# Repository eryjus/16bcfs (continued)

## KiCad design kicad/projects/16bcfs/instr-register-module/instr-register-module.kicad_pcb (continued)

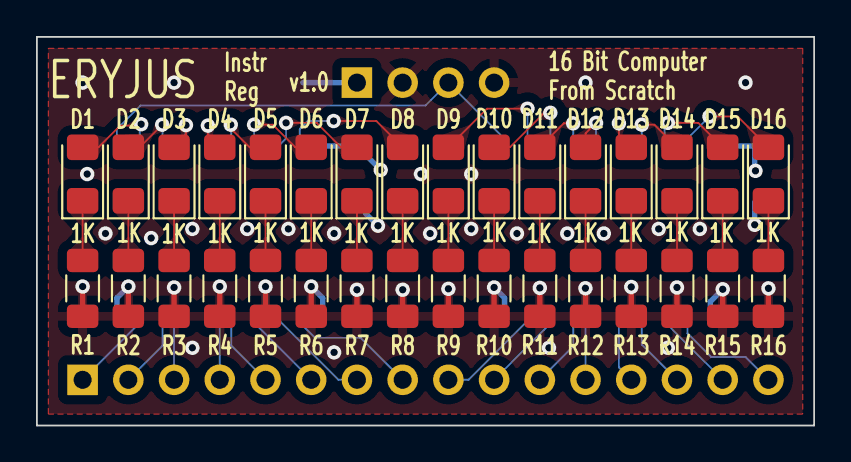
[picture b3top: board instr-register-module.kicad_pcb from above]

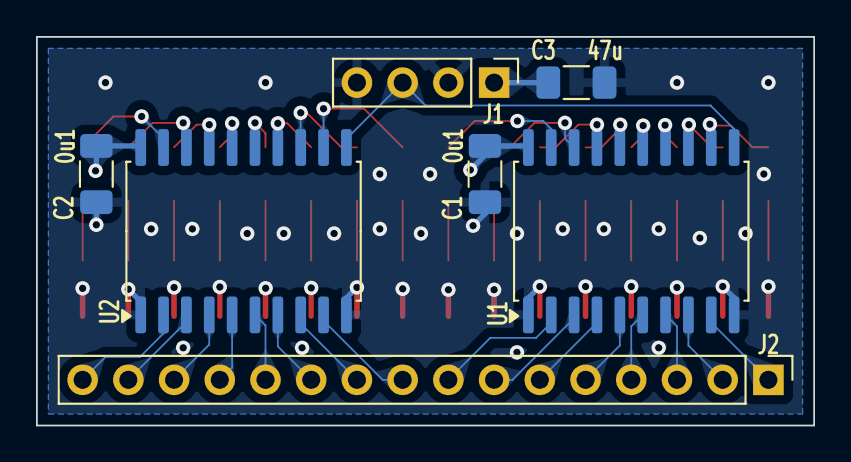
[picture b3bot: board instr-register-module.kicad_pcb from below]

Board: 4 copper layers, 43.2 x 21.6 mm, 39 parts (7 on the bottom side), 51 nets.

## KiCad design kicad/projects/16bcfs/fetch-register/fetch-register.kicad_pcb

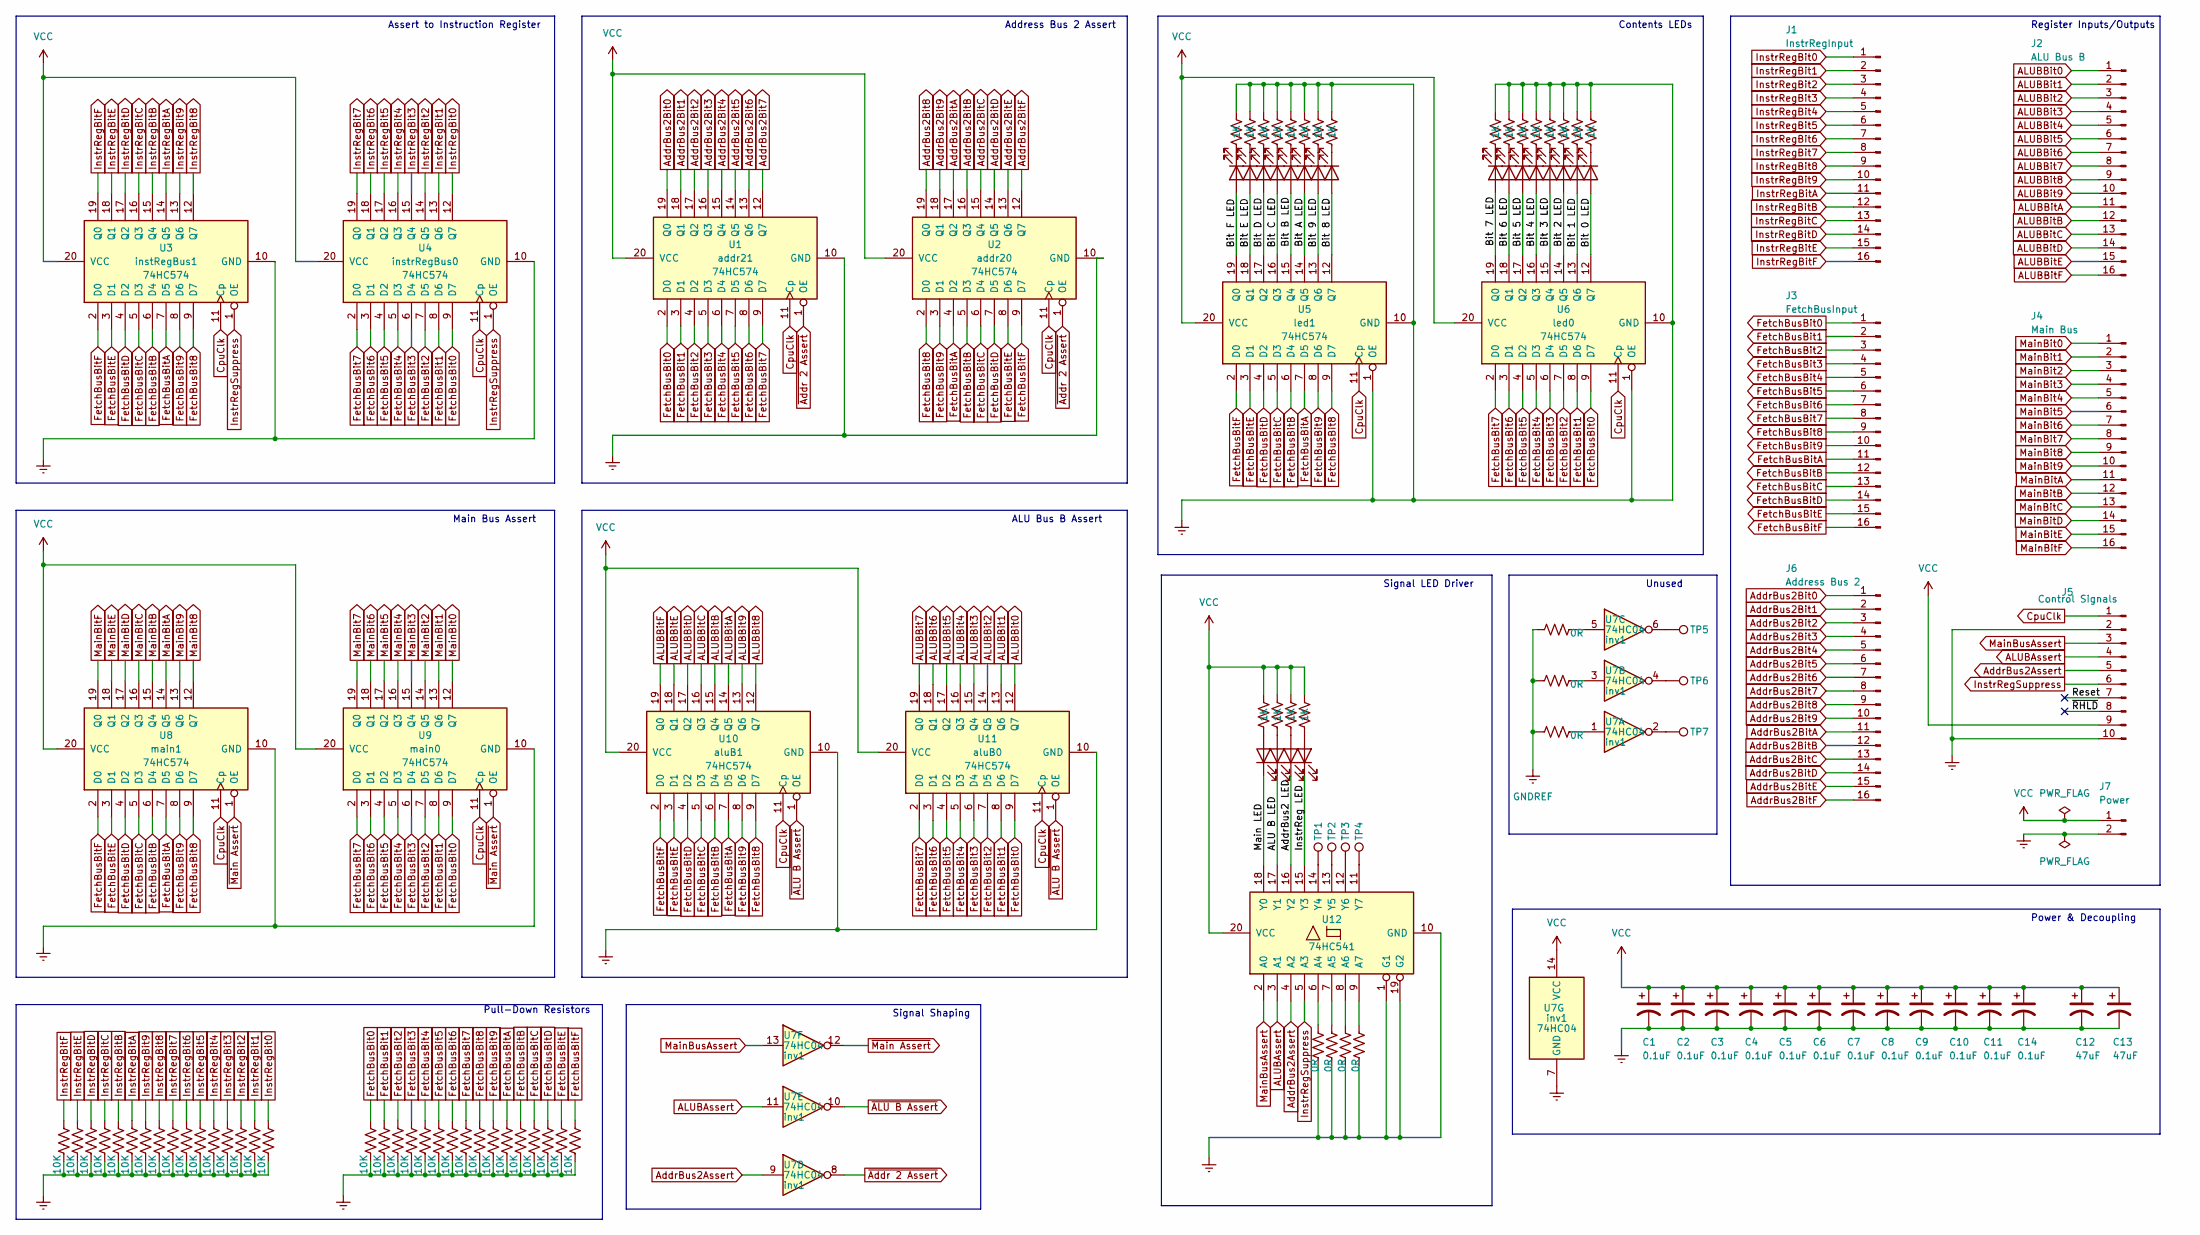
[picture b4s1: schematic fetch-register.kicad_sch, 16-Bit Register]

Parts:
C1, C2, C3, C4, C5, C6, C7, C8, C9, C10, C11, C14: 0.1uF; C_1206_3216Metric_Pad1.33x1.80mm_HandSolder
C12, C13: 47uF; C_1206_3216Metric_Pad1.33x1.80mm_HandSolder
D1, D2, D3, D4, D5, D6, D7, D8, D9, D10, D11, D12, D13, D14, D15, D16: Green; LED_1206_3216Metric_Pad1.42x1.75mm_HandSolder
D17, D18, D19, D20: Red; LED_1206_3216Metric_Pad1.42x1.75mm_HandSolder
J1: InstrRegInput; PinHeader_1x16_P2.54mm_Vertical
J2: ALU Bus B; PinHeader_1x16_P2.54mm_Vertical
J3: FetchBusInput; PinHeader_1x16_P2.54mm_Vertical
J4: Main Bus; PinHeader_1x16_P2.54mm_Vertical
J5: Control Signals; PinHeader_1x10_P2.54mm_Vertical
J6: Address Bus 2; PinHeader_1x16_P2.54mm_Vertical
J7: Power; PinHeader_1x02_P2.54mm_Vertical
R1, R2, R3, R4, R5, R6, R7, R8, R9, R10, R11, R12, R13, R14, R15, R16, R17, R18, R19, R20: 1K; R_1206_3216Metric_Pad1.30x1.75mm_HandSolder
R21, R22, R23, R24, R25, R26, R27, R28, R29, R30, R31, R32, R33, R34, R35, R36, R37, R38, R39, R40, R41, R42, R43, R44, R45, R46, R47, R48, R49, R50, R51, R52: 10K; R_1206_3216Metric_Pad1.30x1.75mm_HandSolder
R53, R54, R55, R56, R57, R58, R59: 0R; R_1206_3216Metric_Pad1.30x1.75mm_HandSolder
TP1, TP2, TP3, TP4, TP5, TP6, TP7: TestPoint; TestPoint_SMD_D0.8mm
U1, U2, U3, U4, U5, U6, U8, U9, U10, U11: 74HC574; SOIC-20W_7.5x12.8mm_P1.27mm
U7: 74HC04; SOIC-14_3.9x8.7mm_P1.27mm
U12: 74HC541; SOIC-20W_7.5x12.8mm_P1.27mm

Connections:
/ALU B LED: D18.1 (K), U12.17 (Y1)
/AddrBus2 LED: D19.1 (K), U12.16 (Y2)
/Bit 0 LED: D16.2 (A), U6.12 (Q7)
/Bit 1 LED: D15.2 (A), U6.13 (Q6)
/Bit 2 LED: D14.2 (A), U6.14 (Q5)
/Bit 3 LED: D13.2 (A), U6.15 (Q4)
/Bit 4 LED: D12.2 (A), U6.16 (Q3)
/Bit 5 LED: D11.2 (A), U6.17 (Q2)
/Bit 6 LED: D10.2 (A), U6.18 (Q1)
/Bit 7 LED: D9.2 (A), U6.19 (Q0)
/Bit 8 LED: D8.2 (A), U5.12 (Q7)
/Bit 9 LED: D7.2 (A), U5.13 (Q6)
/Bit A LED: D6.2 (A), U5.14 (Q5)
/Bit B LED: D5.2 (A), U5.15 (Q4)
/Bit C LED: D4.2 (A), U5.16 (Q3)
/Bit D LED: D3.2 (A), U5.17 (Q2)
/Bit E LED: D2.2 (A), U5.18 (Q1)
/Bit F LED: D1.2 (A), U5.19 (Q0)
/InstrReg LED: D20.1 (K), U12.15 (Y3)
/Main LED: D17.1 (K), U12.18 (Y0)
/Reset: J5.7
/~RHLD: J5.8
ALUBAssert: J5.4, U7.11, U12.3 (A1)
ALUBBit0: J2.1, U11.12 (Q7)
ALUBBit1: J2.2, U11.13 (Q6)
ALUBBit2: J2.3, U11.14 (Q5)
ALUBBit3: J2.4, U11.15 (Q4)
ALUBBit4: J2.5, U11.16 (Q3)
ALUBBit5: J2.6, U11.17 (Q2)
ALUBBit6: J2.7, U11.18 (Q1)
ALUBBit7: J2.8, U11.19 (Q0)
ALUBBit8: J2.9, U10.12 (Q7)
ALUBBit9: J2.10, U10.13 (Q6)
ALUBBitA: J2.11, U10.14 (Q5)
ALUBBitB: J2.12, U10.15 (Q4)
ALUBBitC: J2.13, U10.16 (Q3)
ALUBBitD: J2.14, U10.17 (Q2)
ALUBBitE: J2.15, U10.18 (Q1)
ALUBBitF: J2.16, U10.19 (Q0)
AddrBus2Assert: J5.5, U7.9, U12.4 (A2)
AddrBus2Bit0: J6.1, U1.19 (Q0)
AddrBus2Bit1: J6.2, U1.18 (Q1)
AddrBus2Bit2: J6.3, U1.17 (Q2)
AddrBus2Bit3: J6.4, U1.16 (Q3)
AddrBus2Bit4: J6.5, U1.15 (Q4)
AddrBus2Bit5: J6.6, U1.14 (Q5)
AddrBus2Bit6: J6.7, U1.13 (Q6)
AddrBus2Bit7: J6.8, U1.12 (Q7)
AddrBus2Bit8: J6.9, U2.19 (Q0)
AddrBus2Bit9: J6.10, U2.18 (Q1)
AddrBus2BitA: J6.11, U2.17 (Q2)
AddrBus2BitB: J6.12, U2.16 (Q3)
AddrBus2BitC: J6.13, U2.15 (Q4)
AddrBus2BitD: J6.14, U2.14 (Q5)
AddrBus2BitE: J6.15, U2.13 (Q6)
AddrBus2BitF: J6.16, U2.12 (Q7)
CpuClk: J5.1, U1.11 (Cp), U2.11 (Cp), U3.11 (Cp), U4.11 (Cp), U5.11 (Cp), U6.11 (Cp), U8.11 (Cp), U9.11 (Cp), U10.11 (Cp), U11.11 (Cp)
FetchBusBit0: J3.1, R37.1, U1.2 (D0), U4.9 (D7), U6.9 (D7), U9.9 (D7), U11.9 (D7)
FetchBusBit1: J3.2, R38.1, U1.3 (D1), U4.8 (D6), U6.8 (D6), U9.8 (D6), U11.8 (D6)
FetchBusBit2: J3.3, R39.1, U1.4 (D2), U4.7 (D5), U6.7 (D5), U9.7 (D5), U11.7 (D5)
FetchBusBit3: J3.4, R40.1, U1.5 (D3), U4.6 (D4), U6.6 (D4), U9.6 (D4), U11.6 (D4)
FetchBusBit4: J3.5, R41.1, U1.6 (D4), U4.5 (D3), U6.5 (D3), U9.5 (D3), U11.5 (D3)
FetchBusBit5: J3.6, R42.1, U1.7 (D5), U4.4 (D2), U6.4 (D2), U9.4 (D2), U11.4 (D2)
FetchBusBit6: J3.7, R43.1, U1.8 (D6), U4.3 (D1), U6.3 (D1), U9.3 (D1), U11.3 (D1)
FetchBusBit7: J3.8, R44.1, U1.9 (D7), U4.2 (D0), U6.2 (D0), U9.2 (D0), U11.2 (D0)
FetchBusBit8: J3.9, R45.1, U2.2 (D0), U3.9 (D7), U5.9 (D7), U8.9 (D7), U10.9 (D7)
FetchBusBit9: J3.10, R46.1, U2.3 (D1), U3.8 (D6), U5.8 (D6), U8.8 (D6), U10.8 (D6)
FetchBusBitA: J3.11, R47.1, U2.4 (D2), U3.7 (D5), U5.7 (D5), U8.7 (D5), U10.7 (D5)
FetchBusBitB: J3.12, R48.1, U2.5 (D3), U3.6 (D4), U5.6 (D4), U8.6 (D4), U10.6 (D4)
FetchBusBitC: J3.13, R49.1, U2.6 (D4), U3.5 (D3), U5.5 (D3), U8.5 (D3), U10.5 (D3)
FetchBusBitD: J3.14, R50.1, U2.7 (D5), U3.4 (D2), U5.4 (D2), U8.4 (D2), U10.4 (D2)
FetchBusBitE: J3.15, R51.1, U2.8 (D6), U3.3 (D1), U5.3 (D1), U8.3 (D1), U10.3 (D1)
FetchBusBitF: J3.16, R52.1, U2.9 (D7), U3.2 (D0), U5.2 (D0), U8.2 (D0), U10.2 (D0)
GNDREF: C1.2, C2.2, C3.2, C4.2, C5.2, C6.2, C7.2, C8.2, C9.2, C10.2, C11.2, C12.2, C13.2, C14.2, J5.2, J5.10, J7.2, R1.1, R2.1, R3.1, R4.1, R5.1, R6.1, R7.1, R8.1, R9.1, R10.1, R11.1, R12.1, R13.1, R14.1, R15.1, R16.1, R21.2, R22.2, R23.2, R24.2, R25.2, R26.2, R27.2, R28.2, R29.2, R30.2, R31.2, R32.2, R33.2, R34.2, R35.2, R36.2, R37.2, R38.2, R39.2, R40.2, R41.2, R42.2, R43.2, R44.2, R45.2, R46.2, R47.2, R48.2, R49.2, R50.2, R51.2, R52.2, R53.2, R54.2, R55.2, R56.2, R57.1, R58.1, R59.1, U1.10 (GND), U2.10 (GND), U3.10 (GND), U4.10 (GND), U5.1 (OE), U5.10 (GND), U6.1 (OE), U6.10 (GND), U7.7 (GND), U8.10 (GND), U9.10 (GND), U10.10 (GND), U11.10 (GND), U12.1 (G1), U12.10 (GND), U12.19 (G2)
InstrRegBit0: J1.1, R36.1, U4.12 (Q7)
InstrRegBit1: J1.2, R35.1, U4.13 (Q6)
InstrRegBit2: J1.3, R34.1, U4.14 (Q5)
InstrRegBit3: J1.4, R33.1, U4.15 (Q4)
InstrRegBit4: J1.5, R32.1, U4.16 (Q3)
InstrRegBit5: J1.6, R31.1, U4.17 (Q2)
InstrRegBit6: J1.7, R30.1, U4.18 (Q1)
InstrRegBit7: J1.8, R29.1, U4.19 (Q0)
InstrRegBit8: J1.9, R28.1, U3.12 (Q7)
InstrRegBit9: J1.10, R27.1, U3.13 (Q6)
InstrRegBitA: J1.11, R26.1, U3.14 (Q5)
InstrRegBitB: J1.12, R25.1, U3.15 (Q4)
InstrRegBitC: J1.13, R24.1, U3.16 (Q3)
InstrRegBitD: J1.14, R23.1, U3.17 (Q2)
InstrRegBitE: J1.15, R22.1, U3.18 (Q1)
InstrRegBitF: J1.16, R21.1, U3.19 (Q0)
InstrRegSuppress: J5.6, U3.1 (OE), U4.1 (OE), U12.5 (A3)
MainBit0: J4.1, U9.12 (Q7)
MainBit1: J4.2, U9.13 (Q6)
MainBit2: J4.3, U9.14 (Q5)
MainBit3: J4.4, U9.15 (Q4)
MainBit4: J4.5, U9.16 (Q3)
MainBit5: J4.6, U9.17 (Q2)
MainBit6: J4.7, U9.18 (Q1)
MainBit7: J4.8, U9.19 (Q0)
MainBit8: J4.9, U8.12 (Q7)
MainBit9: J4.10, U8.13 (Q6)
MainBitA: J4.11, U8.14 (Q5)
MainBitB: J4.12, U8.15 (Q4)
MainBitC: J4.13, U8.16 (Q3)
MainBitD: J4.14, U8.17 (Q2)
MainBitE: J4.15, U8.18 (Q1)
MainBitF: J4.16, U8.19 (Q0)
MainBusAssert: J5.3, U7.13, U12.2 (A0)
unnamed: D1.1 (K), R1.2
unnamed: D2.1 (K), R2.2
unnamed: D3.1 (K), R3.2
unnamed: D4.1 (K), R4.2
unnamed: D5.1 (K), R5.2
unnamed: D6.1 (K), R6.2
unnamed: D7.1 (K), R7.2
unnamed: D8.1 (K), R8.2
unnamed: D9.1 (K), R9.2
unnamed: D10.1 (K), R10.2
unnamed: D11.1 (K), R11.2
unnamed: D12.1 (K), R12.2
unnamed: D13.1 (K), R13.2
unnamed: D14.1 (K), R14.2
unnamed: D15.1 (K), R15.2
unnamed: D16.1 (K), R16.2
unnamed: D17.2 (A), R17.2
unnamed: D18.2 (A), R18.2
unnamed: D19.2 (A), R19.2
unnamed: D20.2 (A), R20.2
unnamed: R57.2, U7.1
unnamed: R58.2, U7.3
unnamed: R59.2, U7.5
unnamed: TP5.1, U7.6
unnamed: TP6.1, U7.4
unnamed: TP7.1, U7.2
unnamed: R53.1, U12.6 (A4)
unnamed: R54.1, U12.7 (A5)
unnamed: R55.1, U12.8 (A6)
unnamed: R56.1, U12.9 (A7)
unnamed: TP1.1, U12.14 (Y4)
unnamed: TP2.1, U12.13 (Y5)
unnamed: TP3.1, U12.12 (Y6)
unnamed: TP4.1, U12.11 (Y7)
VCC: C1.1, C2.1, C3.1, C4.1, C5.1, C6.1, C7.1, C8.1, C9.1, C10.1, C11.1, C12.1, C13.1, C14.1, J5.9, J7.1, R17.1, R18.1, R19.1, R20.1, U1.20 (VCC), U2.20 (VCC), U3.20 (VCC), U4.20 (VCC), U5.20 (VCC), U6.20 (VCC), U7.14 (VCC), U8.20 (VCC), U9.20 (VCC), U10.20 (VCC), U11.20 (VCC), U12.20 (VCC)
~ALU B Assert: U7.10, U10.1 (OE), U11.1 (OE)
~Addr 2 Assert: U1.1 (OE), U2.1 (OE), U7.8
~Main Assert: U7.12, U8.1 (OE), U9.1 (OE)

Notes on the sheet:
Contents LEDs
ALU Bus B Assert
Pull-Down Resistors
Signal Shaping
Address Bus 2 Assert
Unused
Signal LED Driver
Power & Decoupling
Main Bus Assert
Register Inputs/Outputs
Assert to Instruction Register

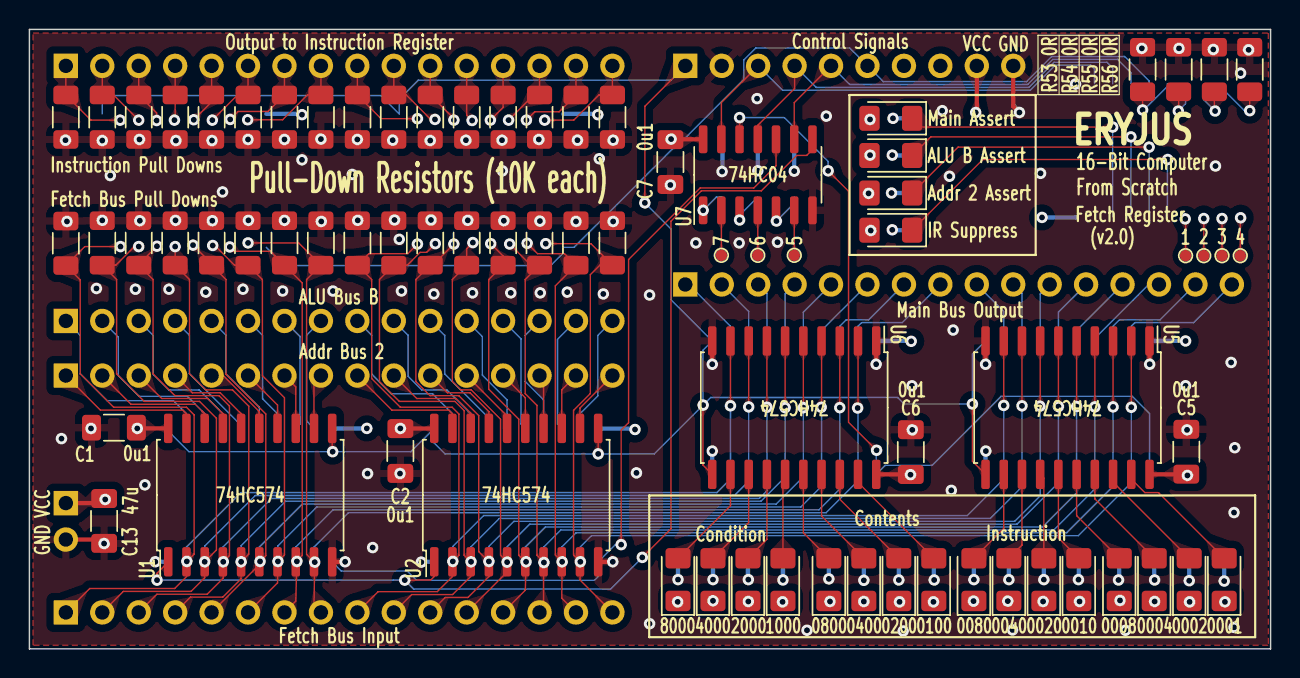
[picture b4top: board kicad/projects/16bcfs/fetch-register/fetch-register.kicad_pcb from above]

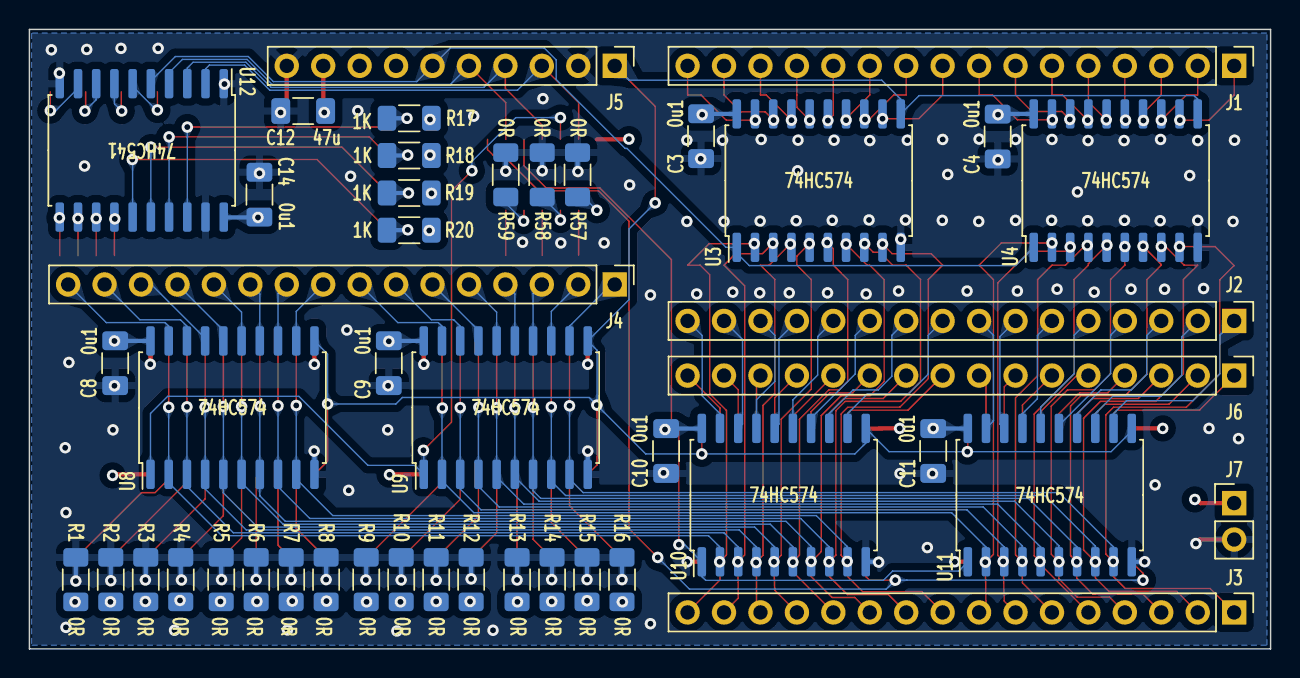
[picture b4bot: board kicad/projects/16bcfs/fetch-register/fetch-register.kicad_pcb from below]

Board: 4 copper layers, 86.5 x 43.2 mm, 119 parts (45 on the bottom side), 144 nets.

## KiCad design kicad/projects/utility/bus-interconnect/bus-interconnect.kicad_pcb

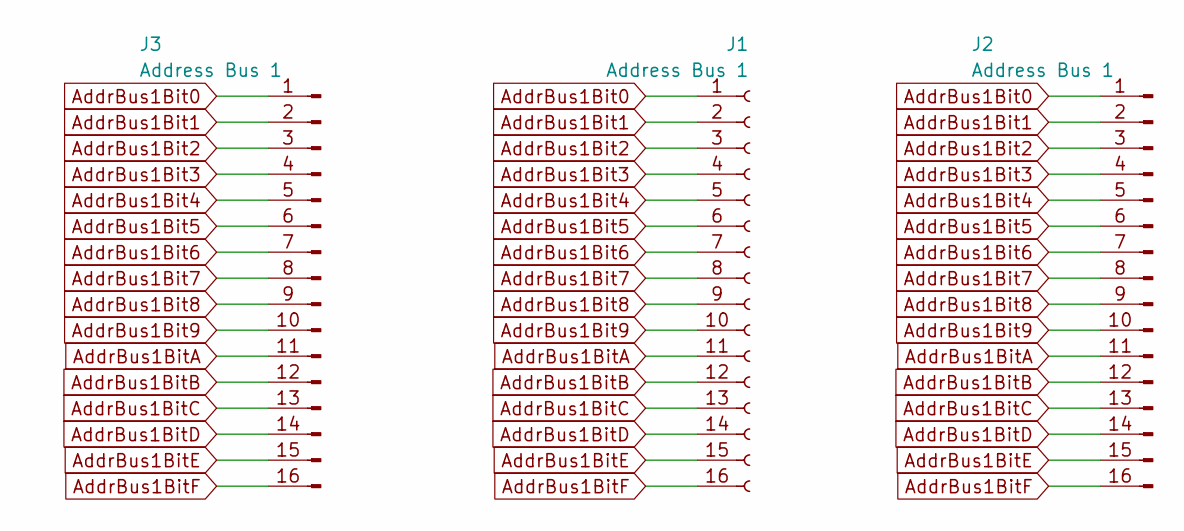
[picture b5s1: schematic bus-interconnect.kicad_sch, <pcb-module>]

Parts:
J1: Address Bus 1; PinSocket_1x16_P2.54mm_Vertical
J2, J3: Address Bus 1; PinHeader_1x16_P2.54mm_Vertical

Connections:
AddrBus1Bit0: J1.1, J2.1, J3.1
AddrBus1Bit1: J1.2, J2.2, J3.2
AddrBus1Bit2: J1.3, J2.3, J3.3
AddrBus1Bit3: J1.4, J2.4, J3.4
AddrBus1Bit4: J1.5, J2.5, J3.5
AddrBus1Bit5: J1.6, J2.6, J3.6
AddrBus1Bit6: J1.7, J2.7, J3.7
AddrBus1Bit7: J1.8, J2.8, J3.8
AddrBus1Bit8: J1.9, J2.9, J3.9
AddrBus1Bit9: J1.10, J2.10, J3.10
AddrBus1BitA: J1.11, J2.11, J3.11
AddrBus1BitB: J1.12, J2.12, J3.12
AddrBus1BitC: J1.13, J2.13, J3.13
AddrBus1BitD: J1.14, J2.14, J3.14
AddrBus1BitE: J1.15, J2.15, J3.15
AddrBus1BitF: J1.16, J2.16, J3.16

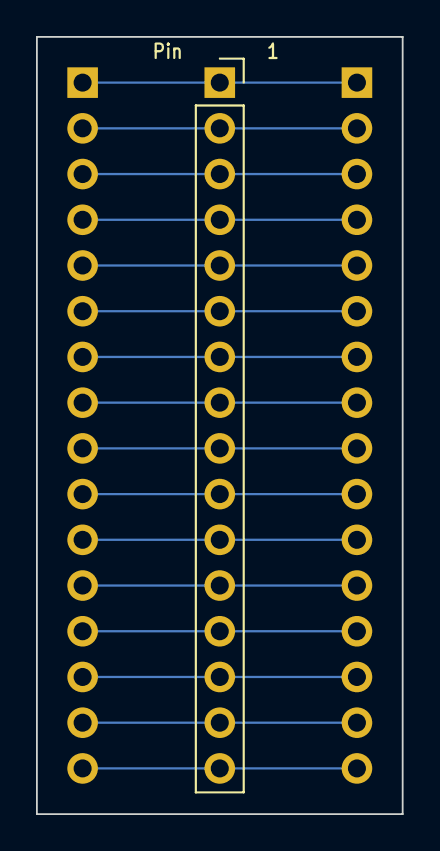
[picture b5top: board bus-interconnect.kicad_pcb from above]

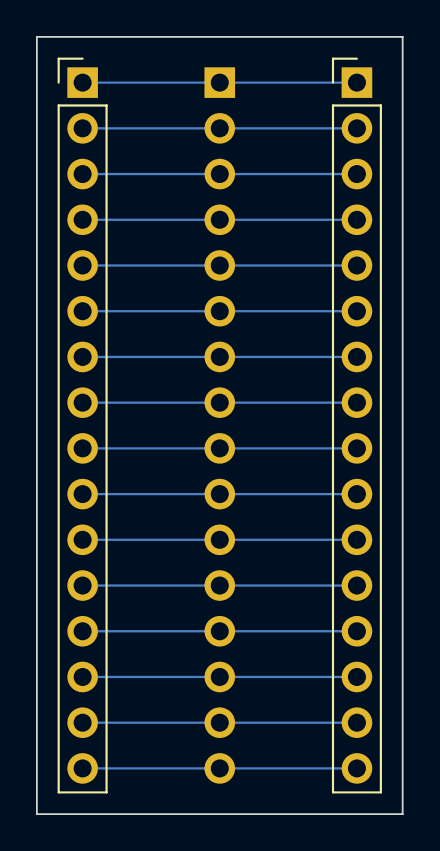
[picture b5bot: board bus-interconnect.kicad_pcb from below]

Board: 2 copper layers, 20.3 x 43.2 mm, 3 parts (2 on the bottom side), 16 nets.

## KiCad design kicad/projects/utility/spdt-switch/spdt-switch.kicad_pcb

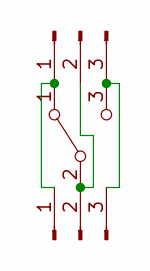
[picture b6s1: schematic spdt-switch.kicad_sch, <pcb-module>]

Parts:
J1, J2: Conn_01x03_Pin; PinHeader_1x03_P2.54mm_Vertical
SW1: SW_SPDT; Microswitch-LXW-5-1-2

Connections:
unnamed: J1.1, J2.1, SW1.1 (A)
unnamed: J1.2, J2.2, SW1.2 (B)
unnamed: J1.3, J2.3, SW1.3 (C)

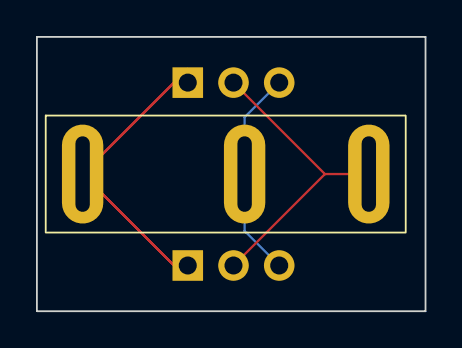
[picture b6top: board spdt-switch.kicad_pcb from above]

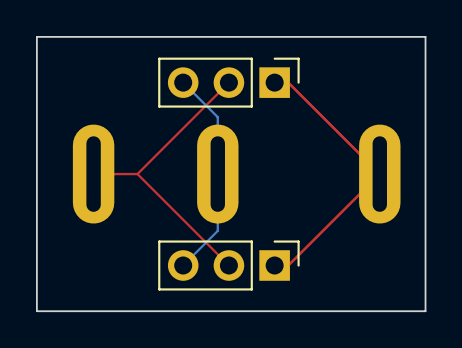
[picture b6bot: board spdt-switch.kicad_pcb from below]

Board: 2 copper layers, 21.6 x 15.2 mm, 3 parts (2 on the bottom side), 3 nets.
